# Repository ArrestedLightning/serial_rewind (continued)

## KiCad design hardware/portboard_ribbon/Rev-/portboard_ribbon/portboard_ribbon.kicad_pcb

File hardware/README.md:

Serial Rewind Hardware
==========

The goal of this project is to eventually support a wide variety of PowerPC Macs.  To do so, a number of different boards are required.  The boards and their statuses are listed below:

|Board|Description|Status|
|-----|-----------|------|
|d1_g3|Main board ("Dash 1" interface) for tray load iMac G3, B&W Power Mac G3, and PCI Graphics Power Mac G4|Mechanical drawing of board in progress, reverse engineering of schematic not yet started.|
|dash2|Main board ("Dash 2" interface) for a wide variety of Macs: Slot load iMac G3, some iBooks, PowerBook G3, Power Mac G4 & Cube.  All machines except iMac G3 and Cube require an additional board to bring the port out.|Working.  Tested on G4 Cube and G4 MDD.|
|main_mini|Main board for Mac Mini G4, eMac G4, possibly others. | Pinout reverse engineered, schematic in progress. |
|portboard_dt|Port breakout board.  Originally intended for G4 towers.  I believe it would also fit in the iBook G3, but this is not tested. | Electrically functional, layout is a work-in-progress.  The goal was to support both the MDD and earlier G4 machines with the same board, but I don't know if that will be possible. |
|portboard_ffc|Generic port breakout board with flat-flex cable connector.   Intended for use with PCI card bracket.| PCB Complete (3D-printed mounting adapter not designed yet)|
|portboard_ribbon|Generic port breakout board with IDC/ribbon cable connector.   Intended for use with PCI card bracket.| PCB Complete (3D-printed mounting adapter not designed yet)|| |
|portboard_img4|Port breakout board for iMac G4.  As far as I know, the iMac G4 is the only machine which uses this form factor.| Designed and manufactured, but not yet fit tested. |
|portboard_mdd|Port breakout board for the Power Mac G4 MDD.  This board replaces the MDD's modem port and mounting bracket.  Unfortunately, there's no great way to mount one side of this board.  Since (as far as I know) every MDD comes with a reversible modem port mounting bracket, it seems like it would make more sense to take advantage of that. |Designed and tested.  Eventually this board may be made obsolete by an updated portboard\_dt. |
|portboard_mini|Port breakout board for Mac Mini G4. | Design not started yet.|

All of these boards use components from my [KiCad libraries project](https://github.com/ArrestedLightning/al_kicad_libraries/).  If you work on any of these boards, I would suggest checking out a copy of that project and adding the libraries to your KiCad globals.

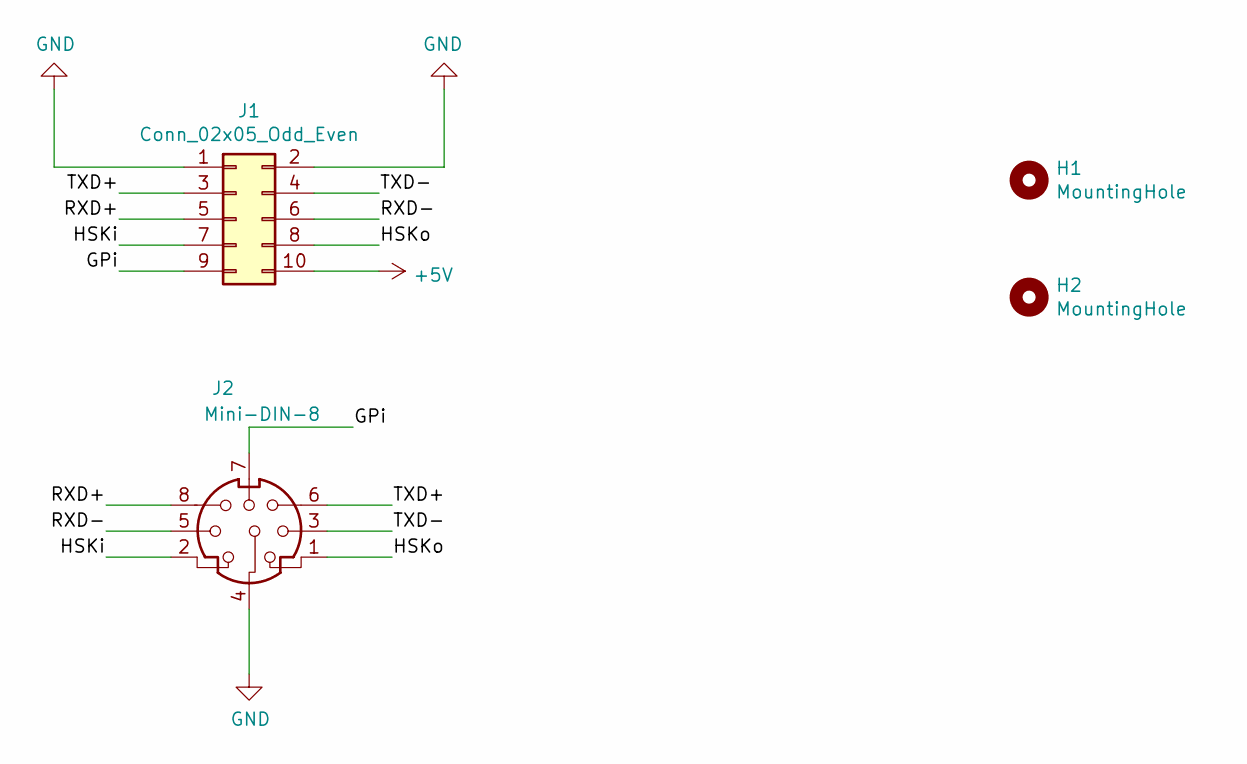
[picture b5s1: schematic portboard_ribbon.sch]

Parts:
H1, H2: MountingHole; MountingHole_3.2mm_M3_Pad
J1: Conn_02x05_Odd_Even; PinHeader_2x05_P2.54mm_Vertical
J2: Mini-DIN-8; MINI_DIN8

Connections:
+5V: J1.10
/GPi: J1.9, J2.7
/HSKi: J1.7, J2.2
/HSKo: J1.8, J2.1
/RXD+: J1.5, J2.8
/RXD-: J1.6, J2.5
/TXD+: J1.3, J2.6
/TXD-: J1.4, J2.3
GND: J1.1, J1.2, J2.4

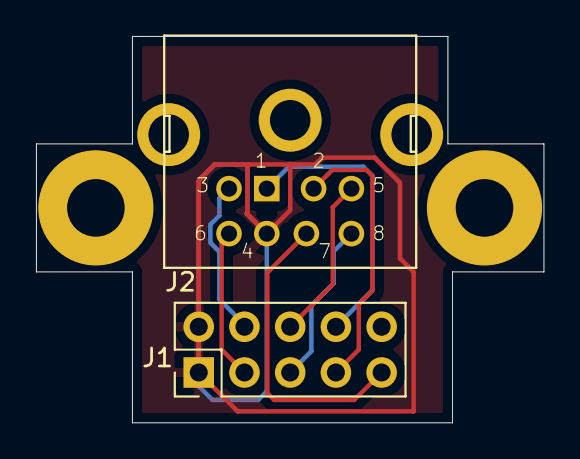
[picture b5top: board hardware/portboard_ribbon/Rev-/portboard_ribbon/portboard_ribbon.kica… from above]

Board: 2 copper layers, 28.2 x 21.5 mm, 4 parts (0 on the bottom side), 8 nets.

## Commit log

2021-10-11 Create LICENSE
2022-06-19 Added latest hardware files.
2022-06-19 Added README file for hardware directory.
2022-06-19 Added README files for each board.
2022-06-19 Updated license to CC-BY-4.0
2022-06-22 Update images
